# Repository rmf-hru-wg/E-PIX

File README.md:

# Control Board 1

## スペック

- ESP32C3@160MHz WiFi+BT5(BT Classicは非対応)
- ICS変換 × 2
- ADC × 2
- BTS6142D 保護回路+ロードスイッチ
- 9DoF IMU AE-BNO055を裏面に搭載可能

## 設計指針

- できるだけ安く　1000円以下
- できるだけ小さく　40mm×40mm
- ICS変換基板の小型化　10mm×8mm
- 無線を使った遠隔操作　WiFi 2.4GHz IEEE 802.11b/g/n

## 今後の方針

- CPUをラズパイなどにして計算性能やカメラの搭載
- ROS2と繋げる

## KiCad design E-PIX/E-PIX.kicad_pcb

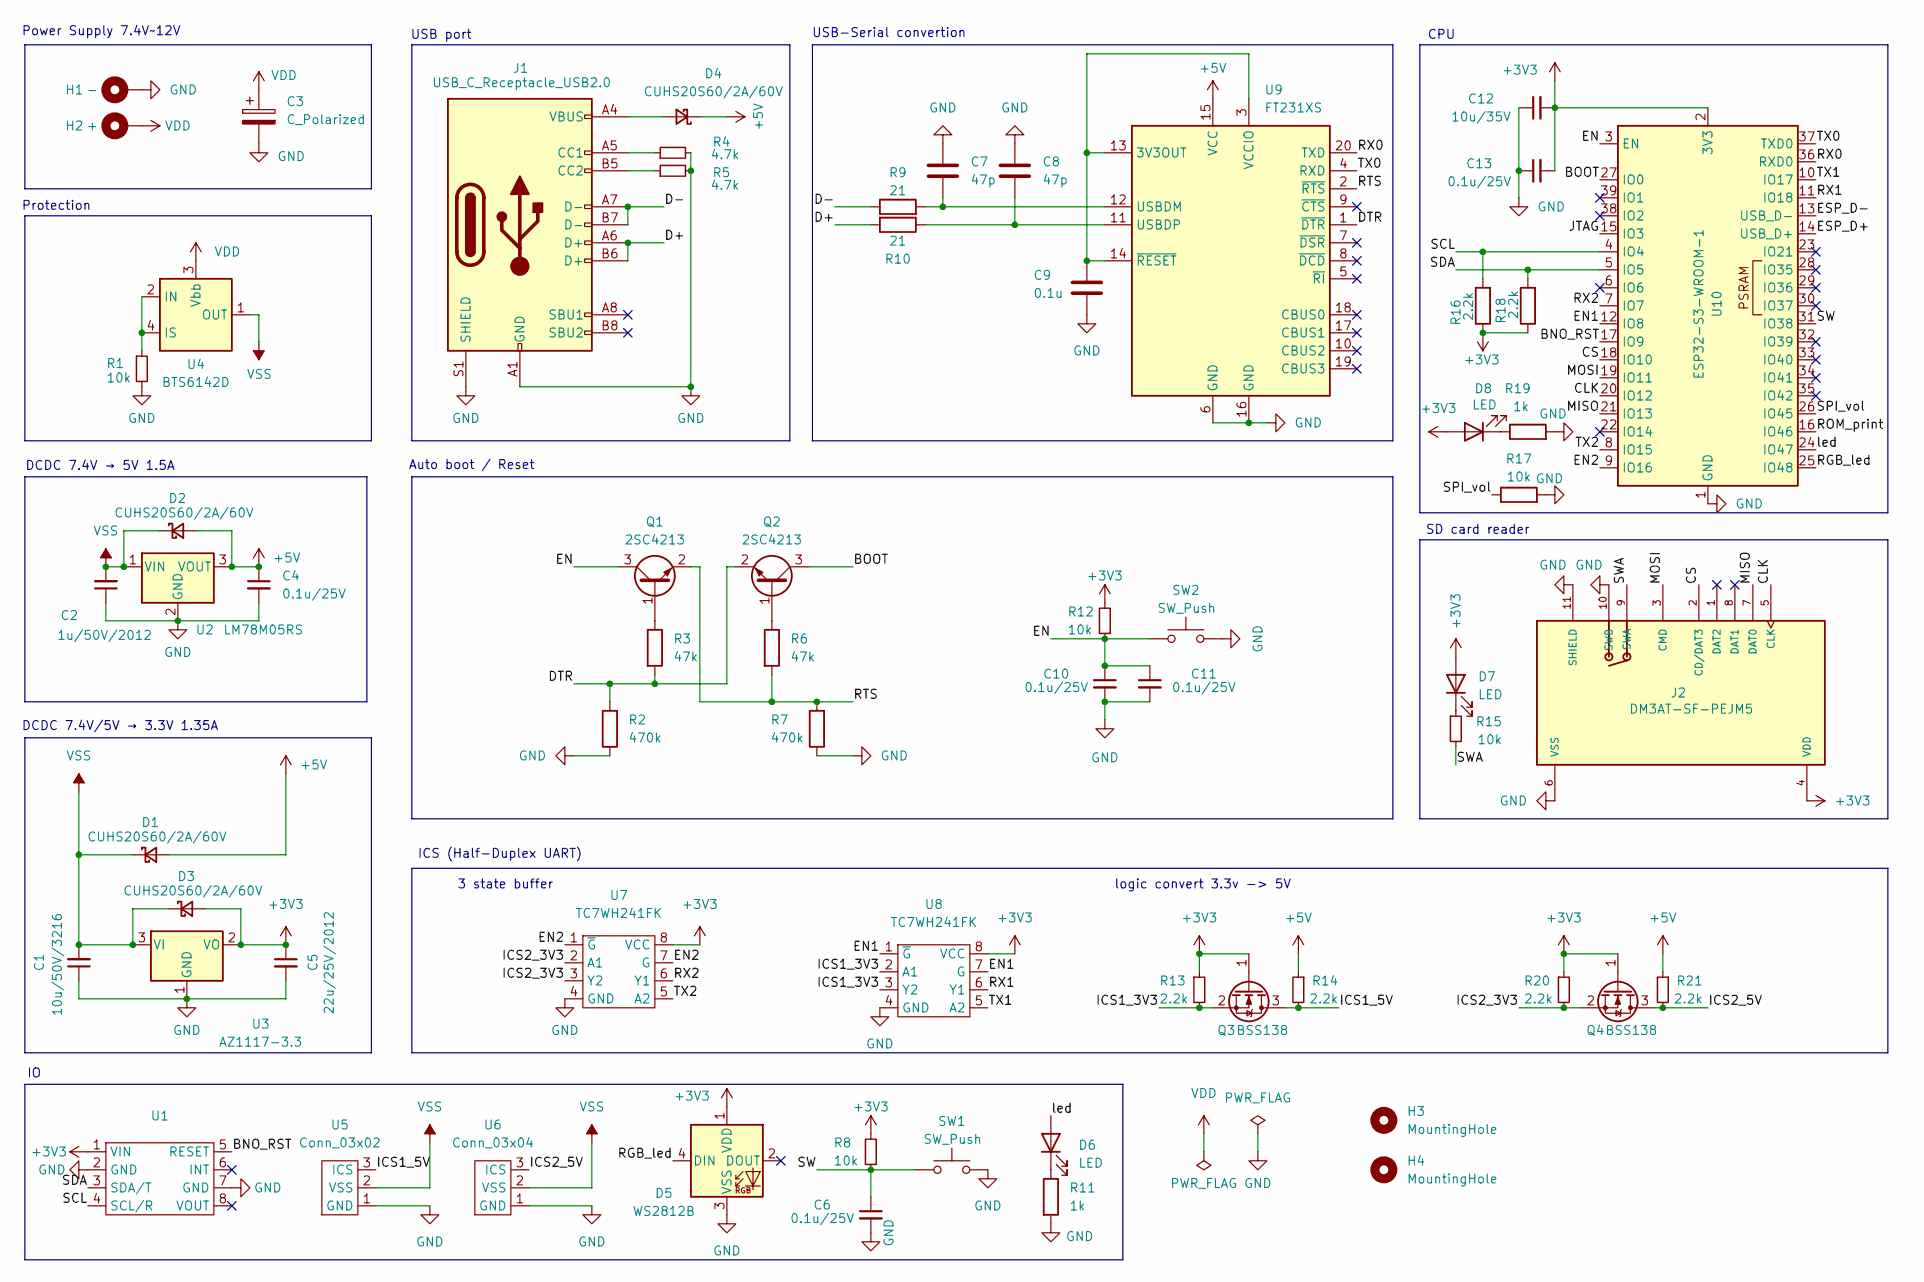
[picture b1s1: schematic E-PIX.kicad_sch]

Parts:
C1: 10u/50V/3216; C_1206_3216Metric
C2: 1u/50V/2012; C_0805_2012Metric
C3: C_Polarized; CP_Radial_D8.0mm_P3.50mm
C4, C6, C10, C11, C13: 0.1u/25V; C_0603_1608Metric
C5: 22u/25V/2012; C_0805_2012Metric
C7, C8: 47p; C_0201_0603Metric
C9: 0.1u; C_0603_1608Metric
C12: 10u/35V; C_1206_3216Metric
D1, D2, D3, D4: CUHS20S60/2A/60V; Diode_US2H
D5: WS2812B; LED_WS2812B_PLCC4_5.0x5.0mm_P3.2mm
D6, D7, D8: LED; LED_0603_1608Metric
H1: -; MountingHole_2.5mm_Pad
H2: +; MountingHole_2.5mm_Pad
H3, H4: MountingHole; MountingHole_3.2mm_M3_DIN965
J1: USB_C_Receptacle_USB2.0; USB_C_Receptacle_XKB_U262-16XN-4BVC11_with_model
J2: DM3AT-SF-PEJM5; microSD_HC_Hirose_DM3AT-SF-PEJM5; PARTREV 20200913
Q1, Q2: 2SC4213; SOT-323_SC-70
Q3, Q4: BSS138; SOT-23
R1, R8, R12, R15, R17: 10k; R_0603_1608Metric
R2, R7: 470k; R_0603_1608Metric
R3, R6: 47k; R_0805_2012Metric
R4, R5: 4.7k; R_0805_2012Metric
R9, R10: 21; R_0603_1608Metric
R11, R19: 1k; R_0805_2012Metric
R13, R14, R20, R21: 2.2k; R_0603_1608Metric
R16, R18: 2.2k; R_0805_2012Metric
SW1, SW2: SW_Push; SW_SKRPACE010
U1: BNO055
U2: LM78M05RS; TO-252-2
U3: AZ1117-3.3; SOT-223-3_TabPin2
U4: BTS6142D; TO-252-4
U5: Conn_03x02; PinHeader_03x02_P2.54mm_Vertical
U6: Conn_03x04; PinHeader_03x04_P2.54mm_Vertical
U7, U8: TC7WH241FK; US-8
U9: FT231XS; SSOP-20_3.9x8.7mm_P0.635mm
U10: ESP32-S3-WROOM-1

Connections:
+3V3: C5.1, C12.2, C13.2, D3.2 (A), D5.1 (VDD), D7.2 (A), D8.2 (A), J2.4 (VDD), Q3.1 (G), Q4.1 (G), R8.2, R12.2, R13.1, R16.1, R18.1, R20.1, U1.1 (VIN), U3.2 (VO), U7.8 (VCC), U8.8 (VCC), U10.2 (3V3)
+5V: C4.1, D1.2 (A), D2.2 (A), D4.1 (K), R14.1, R21.1, U2.3 (VOUT), U9.15 (VCC)
/BNO_RST: U1.5 (RESET), U10.17 (IO9)
/BOOT: Q2.3 (C), U10.27 (IO0)
/CLK: J2.5 (CLK), U10.20 (IO12)
/CS: J2.2 (CD/DAT3), U10.18 (IO10)
/D+: J1.A6 (D+), J1.B6 (D+), R10.2
/D-: J1.A7 (D-), J1.B7 (D-), R9.1
/DTR: Q2.2 (E), R2.2, R3.2, U9.1 (~DTR)
/EN: C10.1, C11.1, Q1.3 (C), R12.1, SW2.1, U10.3 (EN)
/EN1: U8.1 (~G), U8.7 (G), U10.12 (IO8)
/EN2: U7.1 (~G), U7.7 (G), U10.9 (IO16)
/ESP_D+: U10.14 (USB_D+)
/ESP_D-: U10.13 (USB_D-)
/ICS1_3V3: Q3.2 (S), R13.2, U8.2 (A1), U8.3 (Y2)
/ICS1_5V: Q3.3 (D), R14.2, U5.3 (ICS)
/ICS2_3V3: Q4.2 (S), R20.2, U7.2 (A1), U7.3 (Y2)
/ICS2_5V: Q4.3 (D), R21.2, U6.3 (ICS)
/JTAG: U10.15 (IO3)
/MISO: J2.7 (DAT0), U10.21 (IO13)
/MOSI: J2.3 (CMD), U10.19 (IO11)
/RGB_led: D5.4 (DIN), U10.25 (IO48)
/ROM_print: U10.16 (IO46)
/RTS: Q1.2 (E), R6.2, R7.2, U9.2 (~RTS)
/RX0: U9.20 (TXD), U10.36 (RXD0)
/RX1: U8.6 (Y1), U10.11 (IO18)
/RX2: U7.6 (Y1), U10.7 (IO7)
/SCL: R16.2, U1.4 (SCL/R), U10.4 (IO4)
/SDA: R18.2, U1.3 (SDA/T), U10.5 (IO5)
/SPI_vol: R17.1, U10.26 (IO45)
/SW: C6.1, R8.1, SW1.1, U10.31 (IO38)
/SWA: J2.9 (SWA), R15.2
/TX0: U9.4 (RXD), U10.37 (TXD0)
/TX1: U8.5 (A2), U10.10 (IO17)
/TX2: U7.5 (A2), U10.8 (IO15)
/led: D6.2 (A), U10.24 (IO47)
GND: C1.1, C2.1, C3.2, C4.2, C5.2, C6.2, C7.1, C8.1, C9.2, C10.2, C11.2, C12.1, C13.1, D5.3 (VSS), H1.1, J1.A1 (GND), J1.A12 (GND), J1.B1 (GND), J1.B12 (GND), J1.S1 (SHIELD), J2.6 (VSS), J2.10 (SWB), J2.11 (SHIELD), R1.2, R2.1, R4.2, R5.2, R7.1, R11.2, R17.2, R19.2, SW1.2, SW2.2, U1.2 (GND), U1.7 (GND), U2.2 (GND), U3.1 (GND), U5.1 (GND), U6.1 (GND), U7.4 (GND), U8.4 (GND), U9.6 (GND), U9.16 (GND), U10.1 (GND), U10.40 (GND), U10.41 (GND)
unnamed: D4.2 (A), J1.A4 (VBUS), J1.A9 (VBUS), J1.B4 (VBUS), J1.B9 (VBUS)
unnamed: D6.1 (K), R11.1
unnamed: D7.1 (K), R15.1
unnamed: D8.1 (K), R19.1
unnamed: J1.A5 (CC1), R4.1
unnamed: J1.B5 (CC2), R5.1
unnamed: Q1.1 (B), R3.1
unnamed: Q2.1 (B), R6.1
unnamed: R1.1, U4.2 (IN), U4.4 (IS)
unnamed: C9.1, U9.3 (VCCIO), U9.13 (3V3OUT), U9.14 (~RESET)
unnamed: C7.2, R9.2, U9.12 (USBDM)
unnamed: C8.2, R10.1, U9.11 (USBDP)
VDD: C3.1, H2.1, U4.3 (Vbb)
VSS: C1.2, C2.2, D1.1 (K), D2.1 (K), D3.1 (K), U2.1 (VIN), U3.3 (VI), U4.1 (OUT), U4.5 (OUT), U5.2 (VSS), U6.2 (VSS)

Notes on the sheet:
USB-Serial convertion
logic convert 3.3v -> 5V
ICS (Half-Duplex UART)
3 state buffer
CPU
SD card reader
Auto boot / Reset
Protection
DCDC 7.4V → 5V 1.5A
DCDC 7.4V/5V → 3.3V 1.35A
Power Supply 7.4V~12V
USB port

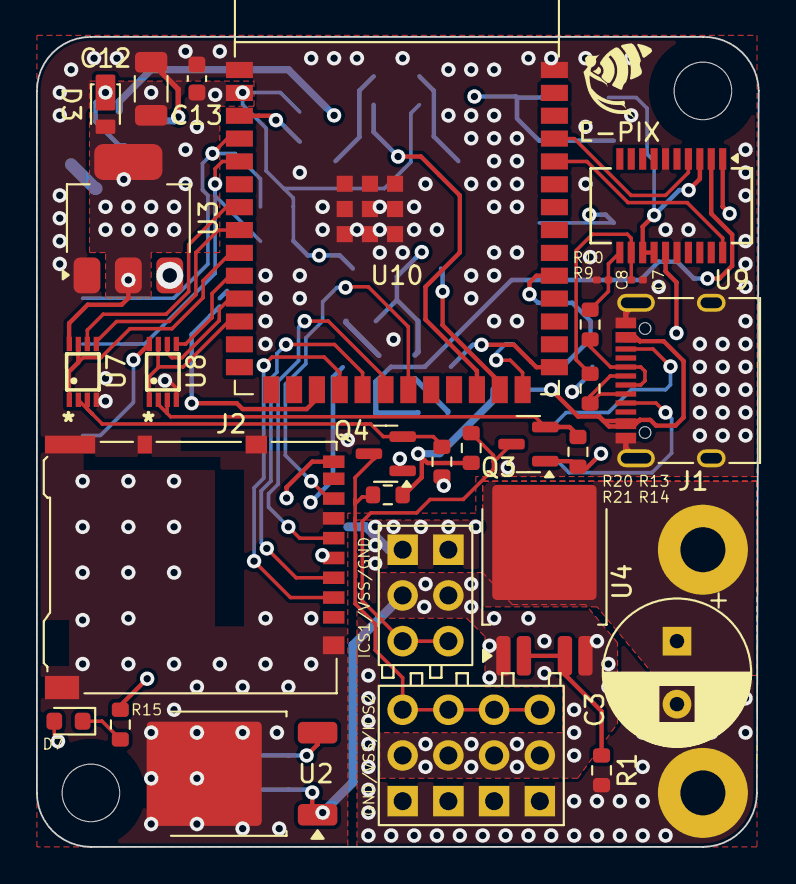
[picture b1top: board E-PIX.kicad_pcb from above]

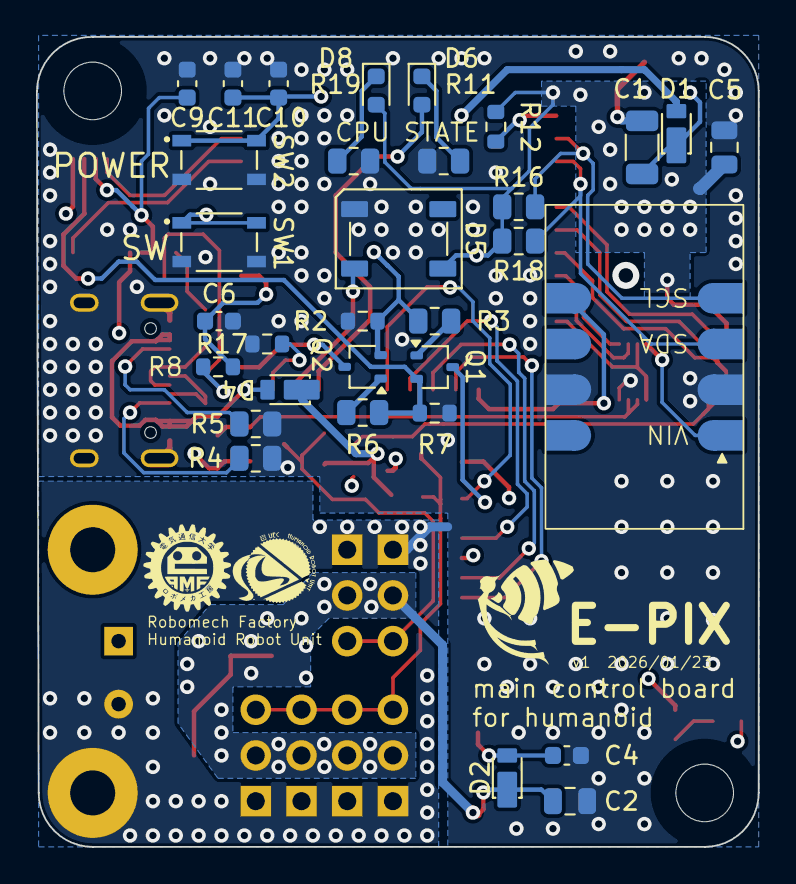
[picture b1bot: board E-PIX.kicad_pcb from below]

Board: 6 copper layers, 40.1 x 45.0 mm, 64 parts (32 on the bottom side), 47 nets.

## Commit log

2025-12-02 update ignore
2025-12-02 add SD card mod
2025-12-02 complete main function. start checking
2025-12-03 finish eeschema. anotate numbers in next step
2025-12-03 finish eeschema. start placing tips
2025-12-05 place 3v3 reg and USB-TTY serial
2025-12-05 update some pin mappings of ESP
2025-12-11 place all the tips
2025-12-11 adjust all the footprints. start trying free routing
2025-12-11 route main wires
2025-12-11 rm auto saved file
2025-12-11 failed free routing
2025-12-11 move some tips
2025-12-12 successfly apply free routing
2025-12-12 create bear
2025-12-15 put silkscreen
2025-12-15 create logo mark.
2025-12-15 update silkscreen. ordered.
2025-12-15 update gitignore
2025-12-15 add ExternalLib as submodule
2025-12-15 update ExternalLib
2025-12-15 add pdf schematic and img
2025-12-15 add step
2026-01-19 add tests
2026-01-20 add test codes for boards
2026-01-20 add few function to wifi connection check
2026-01-20 update few
2026-01-22 fix sketch error
2026-01-22 correct all errors. waiting for check. (order tomorrow)
2026-01-22 modified Externlib
2026-01-22 update sketch pdf
2026-01-23 go thorough last check. order
2026-01-23 order
2026-01-31 check all functions. Confirm both serial1 and serial2
2026-02-02 add code to check all motors
2026-02-05 confirm motor movement
2026-02-15 successfly detect BNO055
2026-02-15 successfly caribrate BNO
